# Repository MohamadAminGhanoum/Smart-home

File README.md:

[BOM - Smart home - BOM.csv](https://github.com/user-attachments/files/24395662/BOM.-.Smart.home.-.BOM.csv)
ESP32 - Smart home project:
--------------------------------
Project description:
This project is a custom-built ESP32-based control to automate a curtain motor and manage multiple devices in my room such as a fan, LED strip, temperature sensor, and additional motors. This is buit using a custom PCB designed in KiCad, using only salvaged components from old electronics but also used Arduino uno for the code

Video: https://www.youtube.com/shorts/h7QkvN7-KNk

The project focuses mainly on hardware design, PCB routing and building in Kicad, reusing components, and experimentation, but not so much software work.
"Note, the main code is not fully written by me, and it is not the main focus of this project. It is only here for reference or experimenting."

Why i mainly made this project:
I wanted to make this project to:
- Learn how to design PCB
- Searching schematics for components and reusing the components from devices
- Build something practical that i can use in my everyday life.

Below is the schematic diagram: Note: im missing 2 resistors, since i could not find the exact symbol for the motor driver that was in the robot-vacuum board.

Below is the pcb that i etched myself:

This is the wiring diagram of the pcb:

These are all materials that i used in the project, u can also access it in the repo

Final reflection
-------------------------------------------
I think that this project for me honestly was difficult. This was my first time using kicad to create a pcb and schematic, and i did some issues, like forgetting to make a schematic and jumping directly to pcb. I had to do many retries to get to my final result. I did much experimenting with trasferring the ink from paper to pcb. I ended up printing the pcb-layout on the paper 3 times through printer, since i twas a normal paper

I further also did not log the hours that i took me to find the ldo voltage regulator from a motherboard, and the time taken to research the different parts from the robot vacuum, because i dont think this counts.

I finally did enjoy making this project, and it was both entertaining and taught me how pcbs are made. If i had to redo this, I think i would put money in getting glossy paper, because they would have made this a lot easier by transferring the ink from the printer directly to pcb.

This project was overall successful, although I had some errors and mistakes. It hepled me with learning how to make PCBs, how to reuse unknow parts by lookin in their schematics, how to connect the ESP32, and at last it needed a lot of creativity to work.

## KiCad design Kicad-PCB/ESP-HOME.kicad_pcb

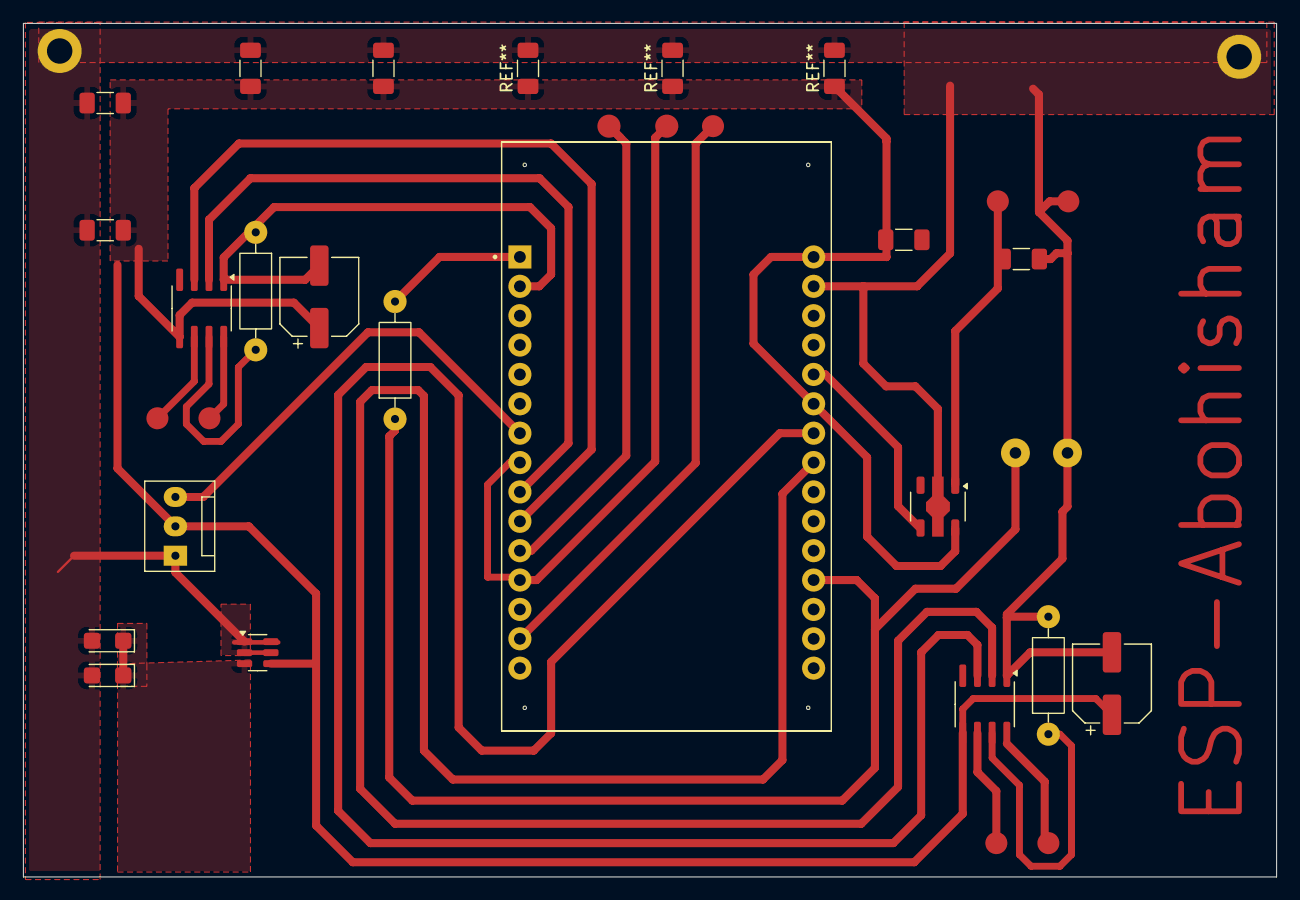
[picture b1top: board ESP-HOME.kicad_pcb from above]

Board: 2 copper layers, 108.4 x 73.8 mm, 3 parts (0 on the bottom side), 3 nets.

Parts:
M2: Fan_3pin; FanPinHeader_1x03_P2.54mm_Vertical
TH1: Thermistor
U1: ESP32-DEVKIT-V1; MODULE_ESP32_DEVKIT_V1

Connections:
GND: M2.1 (-), TH1.1, U1.2 (GND), U1.29 (GND)
unnamed: TH1.2, U1.19 (D34)
g: M2.2 (+), U1.25 (D27), U1.30 (VIN)

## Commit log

2025-12-19 Create Main code
    this is the code i uploaded to esp32
2025-12-22 Add project overview to README
    Added project description for mini smart-home.
2025-12-22 Revise README with project details and components
    Expanded project description with detailed components and functionality, including motor, fan, temperature sensor, LED strip, and PCB etching process.
2025-12-22 Add image placeholder to README
    Added an image placeholder to the README.
2025-12-22 Update image link in README
2025-12-22 Revise README with project details and code note
    Updated project description and clarified code ownership.
2025-12-22 Enhance README with project details and components
    Updated README to provide detailed project description, objectives, and component list for the ESP32 smart home project.
2025-12-22 Add project journal detailing hardware development
    Documented the process and challenges faced while building a project involving a curtain motor, fan, temperature sensor, LED strip, and PCB etching.
2025-12-22 Revise README to mention Arduino Uno integration
    Updated project description to include Arduino Uno usage.
2025-12-22 Add video link to README for project overview
    Added a video link for project demonstration.
2025-12-23 Update README with schematic and PCB diagrams
    Added schematic and PCB images to README.
2025-12-23 Update README with note on schematic diagram
    Added a note about missing resistors in the schematic diagram.
2026-01-17 Rename ESP-HOME.kicad_pcb to Kicad-PCB/ESP-HOME.kicad_pcb
2026-01-17 Rename ESP-HOME.kicad_pro to Kicad-PCB/ESP-HOME.kicad_pro
2026-01-17 Rename ESP-HOME.kicad_sch to Kicad-PCB/ESP-HOME.kicad_sch
2026-01-17 Rename Journal.md to Journal/Journal.md
2026-01-17 Rename Journal.pdf to Journal/Journal.pdf
2026-01-17 Rename Main code to Code/Main code
